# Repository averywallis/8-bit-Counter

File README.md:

# 8-bit Counter
 A simple 8-bit Binary Counter powered by AA batteries.
 This repo includes the KiCad design files

This project is a simple 8-bit counter using two 4-bit counter ICs. Powered by AA batteries and connected to LEDs, it visually displays counting up to 8-bits in binary. This works as a cool little visual display that can be displayed around the house or in a MakerSpace. It has no functional purpose, it is purely for display reasons only.

This project is also available on Hackaday at https://hackaday.io/project/168946-8-bit-counter

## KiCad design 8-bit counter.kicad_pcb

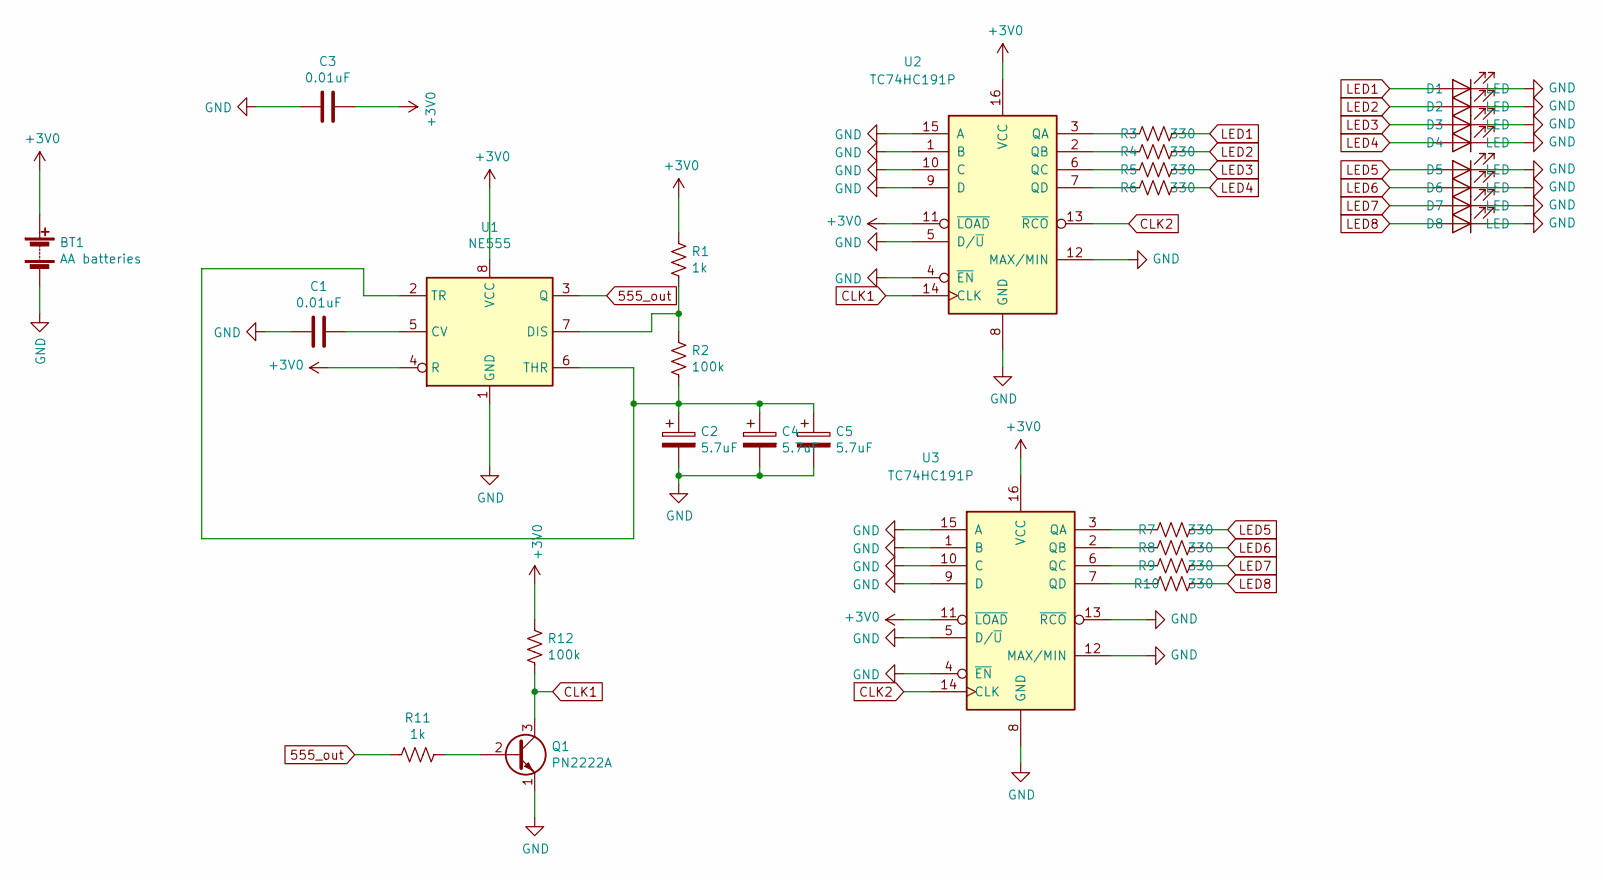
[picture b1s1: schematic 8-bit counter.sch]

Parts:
BT1: AA batteries; BatteryHolder_Keystone_2462_2xAA; MPN 2474
C1, C3: 0.01uF; C_Disc_D8.0mm_W2.5mm_P5.00mm; MPN K103K15X7RF53L2
C2, C4, C5: 5.7uF; CP_Radial_D5.0mm_P2.50mm; MPN 475CKR050M
D1, D2, D3, D4, D5, D6, D7, D8: LED; LED_D5.0mm; MPN LTL-1CHEE
Q1: PN2222A; TO-92_Inline; MPN PN2222ATF
R1, R11: 1k; R_Axial_DIN0207_L6.3mm_D2.5mm_P10.16mm_Horizontal; MPN CF14JT1K00
R2, R12: 100k; R_Axial_DIN0207_L6.3mm_D2.5mm_P10.16mm_Horizontal; MPN CF14JT100K
R3, R4, R5, R6, R7, R8, R9, R10: 330; R_Axial_DIN0207_L6.3mm_D2.5mm_P10.16mm_Horizontal; MPN CFM14JT330R
U1: NE555; DIP-8_W7.62mm; MPN NE555P
U2, U3: TC74HC191P; DIP-16_W7.62mm; MPN CD74HCT191E

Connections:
555_out: R11.2, U1.3 (Q)
+3V0: BT1.1 (+), C3.1, R1.1, R12.2, U1.4 (R), U1.8 (VCC), U2.11 (~LOAD), U2.16 (VCC), U3.11 (~LOAD), U3.16 (VCC)
CLK1: Q1.3 (C), R12.1, U2.14 (CLK)
CLK2: U2.13 (~RCO), U3.14 (CLK)
GND: BT1.2 (-), C1.2, C2.2, C3.2, C4.2, C5.2, D1.1 (K), D2.1 (K), D3.1 (K), D4.1 (K), D5.1 (K), D6.1 (K), D7.1 (K), D8.1 (K), Q1.1 (E), U1.1 (GND), U2.1 (B), U2.4 (~EN), U2.5 (D/~U), U2.8 (GND), U2.9 (D), U2.10 (C), U2.12 (MAX/MIN), U2.15 (A), U3.1 (B), U3.4 (~EN), U3.5 (D/~U), U3.8 (GND), U3.9 (D), U3.10 (C), U3.12 (MAX/MIN), U3.13 (~RCO), U3.15 (A)
LED1: D1.2 (A), R3.1
LED2: D2.2 (A), R4.1
LED3: D3.2 (A), R5.1
LED4: D4.2 (A), R6.1
LED5: D5.2 (A), R7.1
LED6: D6.2 (A), R8.1
LED7: D7.2 (A), R9.1
LED8: D8.2 (A), R10.1
unnamed: C1.1, U1.5 (CV)
unnamed: C2.1, C4.1, C5.1, R2.2, U1.2 (TR), U1.6 (THR)
unnamed: Q1.2 (B), R11.1
unnamed: R1.2, R2.1, U1.7 (DIS)
unnamed: R3.2, U2.3 (QA)
unnamed: R4.2, U2.2 (QB)
unnamed: R5.2, U2.6 (QC)
unnamed: R6.2, U2.7 (QD)
unnamed: R7.2, U3.3 (QA)
unnamed: R8.2, U3.2 (QB)
unnamed: R9.2, U3.6 (QC)
unnamed: R10.2, U3.7 (QD)

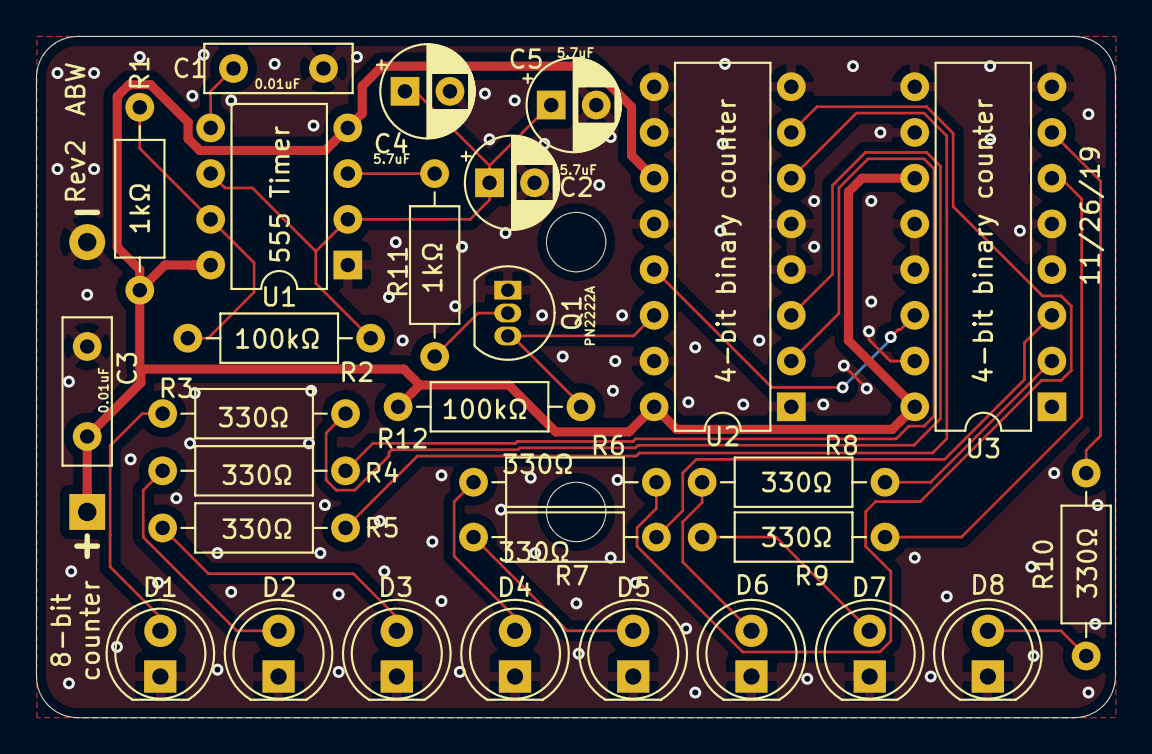
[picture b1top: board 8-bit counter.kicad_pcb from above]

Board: 2 copper layers, 59.9 x 37.8 mm, 30 parts (1 on the bottom side), 25 nets.

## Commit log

2020-01-06 Reorganizing Github
2022-01-29 Create LICENSE
